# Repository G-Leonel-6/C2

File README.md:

# C2
En este repositorio se guardaran los archivos correspondientes al desarrollo de una fuente de alimentacion regulada

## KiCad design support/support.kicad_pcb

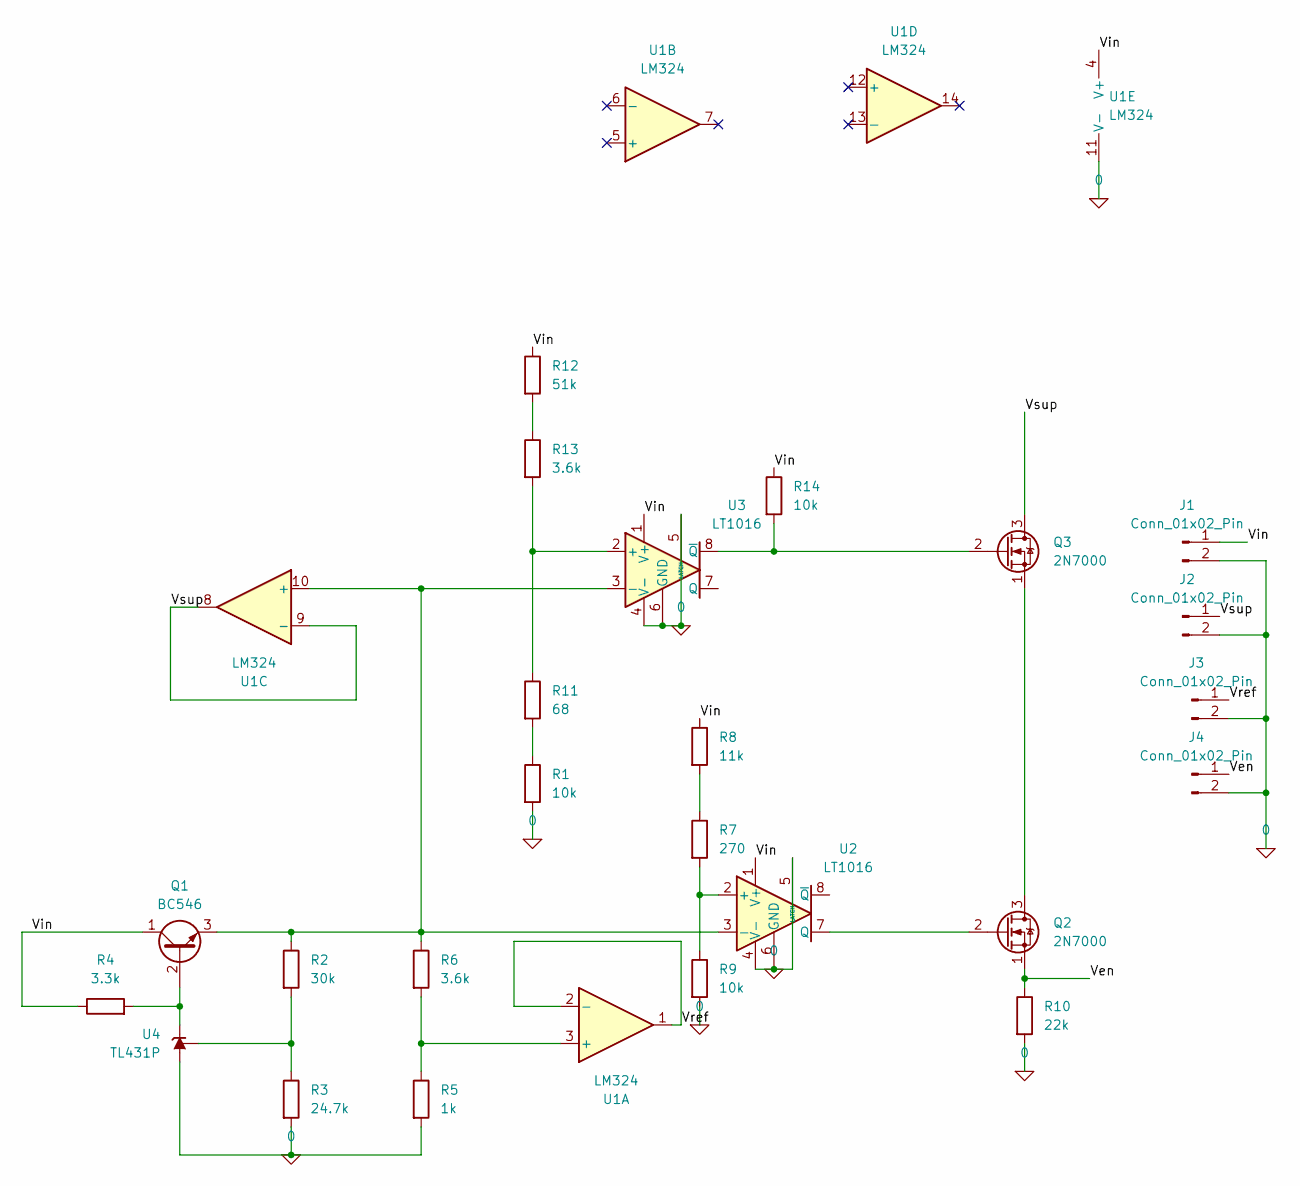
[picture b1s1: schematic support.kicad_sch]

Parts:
J1, J2, J3, J4: Conn_01x02_Pin; TerminalBlock_Altech_AK300-2_P5.00mm
Q1: BC546; TO-92_Inline
Q2, Q3: 2N7000; TO-92_Inline
R1, R9, R14: 10k; R_Axial_DIN0207_L6.3mm_D2.5mm_P10.16mm_Horizontal
R2: 30k; R_Axial_DIN0207_L6.3mm_D2.5mm_P10.16mm_Horizontal
R3: 24.7k; R_Axial_DIN0207_L6.3mm_D2.5mm_P10.16mm_Horizontal
R4: 3.3k; R_Axial_DIN0207_L6.3mm_D2.5mm_P10.16mm_Horizontal
R5: 1k; R_Axial_DIN0207_L6.3mm_D2.5mm_P10.16mm_Horizontal
R6, R13: 3.6k; R_Axial_DIN0207_L6.3mm_D2.5mm_P10.16mm_Horizontal
R7: 270; R_Axial_DIN0207_L6.3mm_D2.5mm_P10.16mm_Horizontal
R8: 11k; R_Axial_DIN0207_L6.3mm_D2.5mm_P10.16mm_Horizontal
R10: 22k; R_Axial_DIN0207_L6.3mm_D2.5mm_P10.16mm_Horizontal
R11: 68; R_Axial_DIN0207_L6.3mm_D2.5mm_P10.16mm_Horizontal
R12: 51k; R_Axial_DIN0207_L6.3mm_D2.5mm_P10.16mm_Horizontal
U1: LM324; DIP-14_W7.62mm_Socket_LongPads
U2, U3: LT1016; DIP-8_W7.62mm_Socket_LongPads
U4: TL431P; DIP-8_W7.62mm

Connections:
0: J1.2, J2.2, J3.2, J4.2, R1.2, R3.2, R5.2, R9.2, R10.2, U1.11 (V-), U2.4 (V-), U2.5 (LATCH), U2.6 (GND), U3.4 (V-), U3.5 (LATCH), U3.6 (GND), U4.6 (A)
/Ven: J4.1, Q2.1 (S), R10.1
/Vin: J1.1, Q1.1 (C), R4.1, R8.1, R12.1, R14.1, U1.4 (V+), U2.1 (V+), U3.1 (V+)
/Vref: J3.1, U1.1, U1.2 (-)
/Vsup: J2.1, Q3.3 (D), U1.8, U1.9 (-)
unnamed: Q1.2 (B), R4.2, U4.1 (K)
unnamed: Q1.3 (E), R2.1, R6.1, U1.10 (+), U2.3 (-), U3.3 (-)
unnamed: Q2.3 (D), Q3.1 (S)
unnamed: Q2.2 (G), U2.7 (Q)
unnamed: Q3.2 (G), R14.2, U3.8 (~Q)
unnamed: R1.1, R11.2
unnamed: R7.1, R8.2
unnamed: R12.2, R13.1
unnamed: R5.1, R6.2, U1.3 (+)
unnamed: R7.2, R9.1, U2.2 (+)
unnamed: R11.1, R13.2, U3.2 (+)
unnamed: R2.2, R3.1, U4.8 (REF)

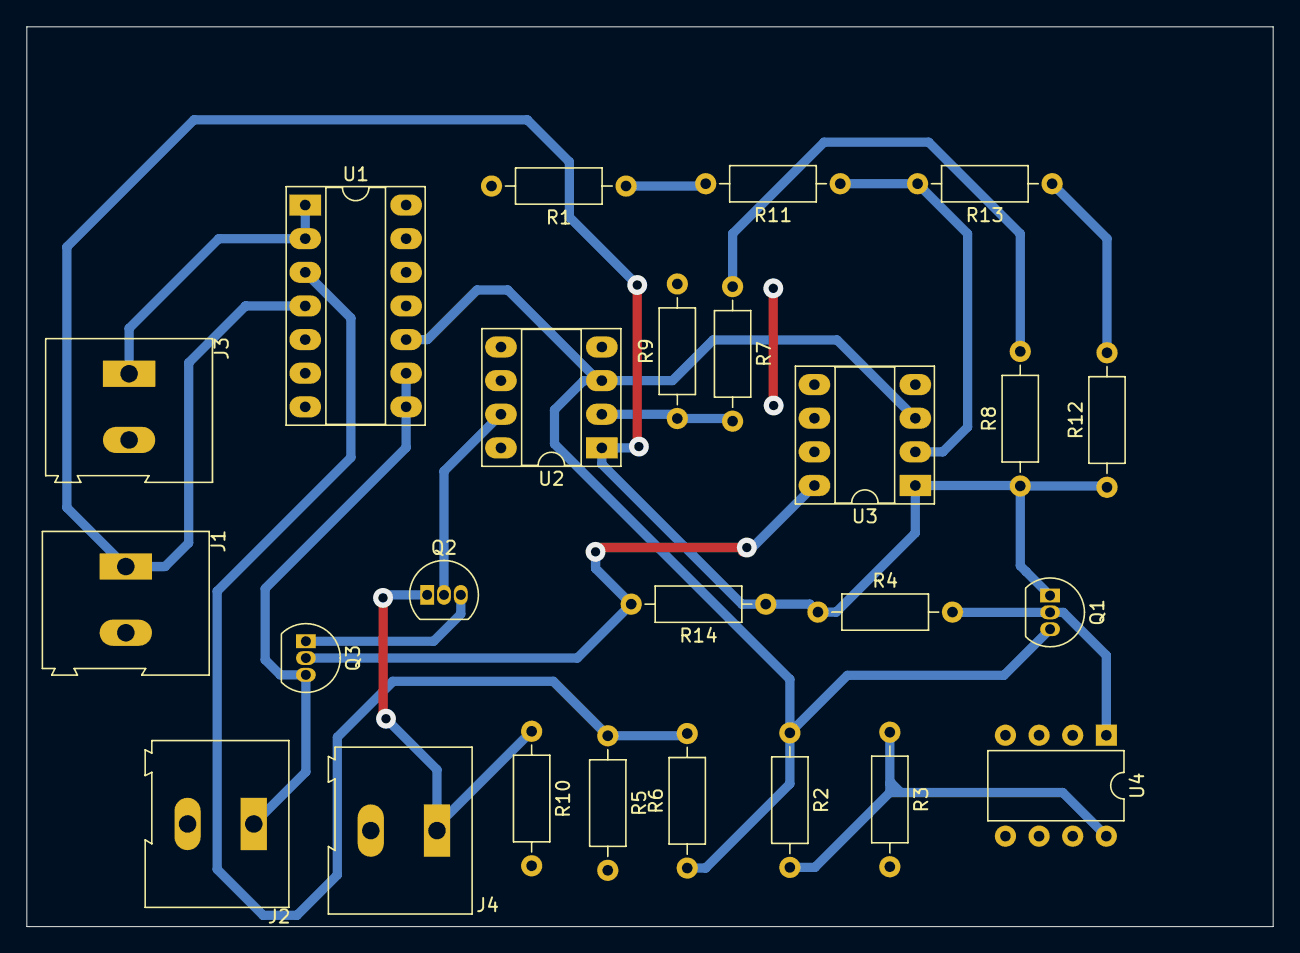
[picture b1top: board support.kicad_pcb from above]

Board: 2 copper layers, 94.1 x 68.0 mm, 25 parts (0 on the bottom side), 17 nets.

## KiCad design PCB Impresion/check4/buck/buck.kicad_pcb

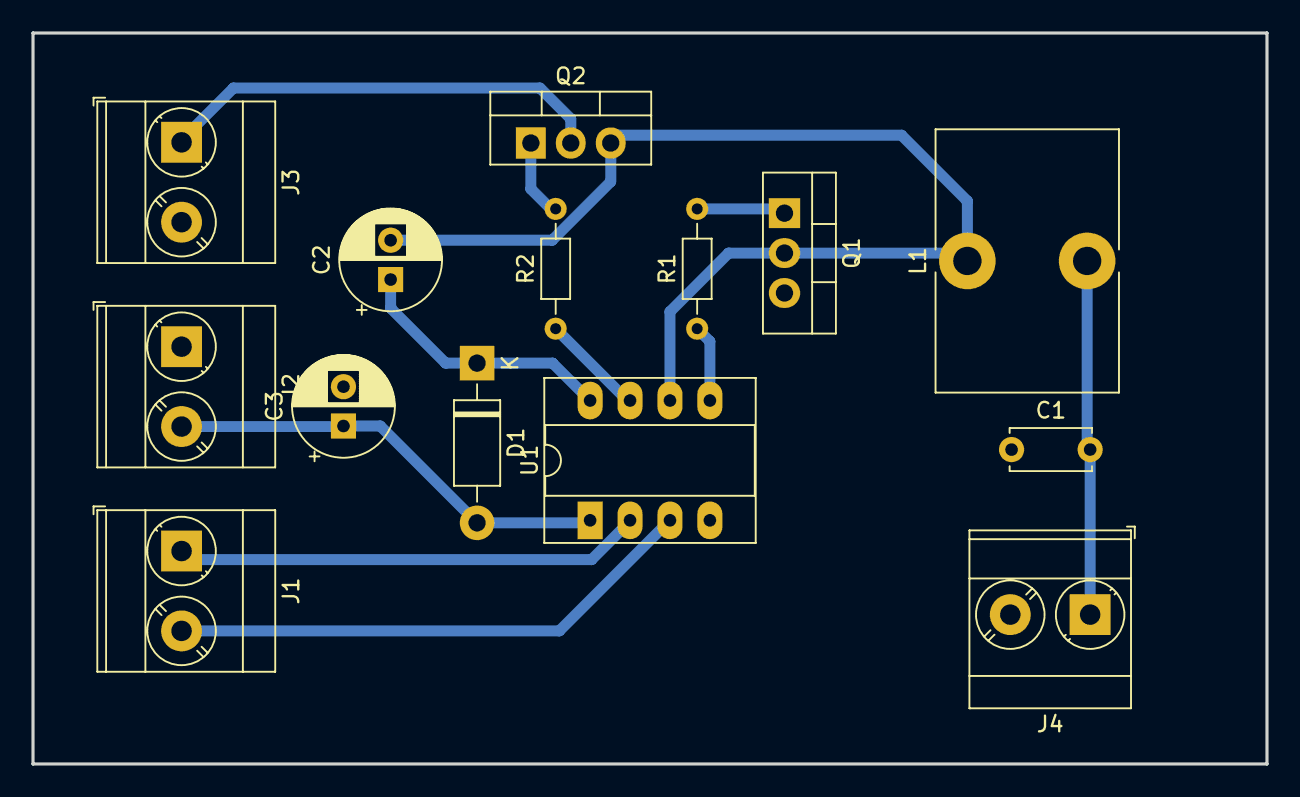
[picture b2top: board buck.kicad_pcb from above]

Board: 2 copper layers, 78.5 x 46.5 mm, 14 parts (0 on the bottom side), 12 nets.

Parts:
C1: 2.7u; C_Disc_D5.0mm_W2.5mm_P5.00mm
C2: 22u; CP_Radial_D6.3mm_P2.50mm
C3: 10u; CP_Radial_D6.3mm_P2.50mm
D1: 1N5819; D_DO-41_SOD81_P10.16mm_Horizontal
J1: V; TerminalBlock_Phoenix_MKDS-3-2-5.08_1x02_P5.08mm_Horizontal
J2: VCC; TerminalBlock_Phoenix_MKDS-3-2-5.08_1x02_P5.08mm_Horizontal
J3: VIN; TerminalBlock_Phoenix_MKDS-3-2-5.08_1x02_P5.08mm_Horizontal
J4: OUT; TerminalBlock_Phoenix_MKDS-3-2-5.08_1x02_P5.08mm_Horizontal
L1: 200u; L_Toroid_Vertical_L16.5mm_W11.4mm_P7.62mm_Pulse_KM-2
Q1, Q2: IRF3205; TO-220-3_Vertical
R1, R2: 10; R_Axial_DIN0204_L3.6mm_D1.6mm_P7.62mm_Horizontal
U1: IR2104; CERDIP-8_W7.62mm_SideBrazed_LongPads_Socket

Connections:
GND: C1.1, C3.2, J2.1, J3.1, J4.2, Q1.3 (S), U1.4 (COM)
Ho: Q2.1 (G), R2.2
Lo: Q1.1 (G), R1.2
unnamed: C2.1, D1.1 (K), U1.8 (VB)
unnamed: J1.2, U1.3 (~SD)
unnamed: J1.1, U1.2 (IN)
unnamed: J3.2, Q2.2 (D)
unnamed: C1.2, J4.1, L1.2
unnamed: R2.1, U1.7 (HO)
unnamed: R1.1, U1.5 (LO)
Vcc: C3.1, D1.2 (A), J2.2, U1.1 (VCC)
Vs: C2.2, L1.1, Q1.2 (D), Q2.3 (S), U1.6 (VS)

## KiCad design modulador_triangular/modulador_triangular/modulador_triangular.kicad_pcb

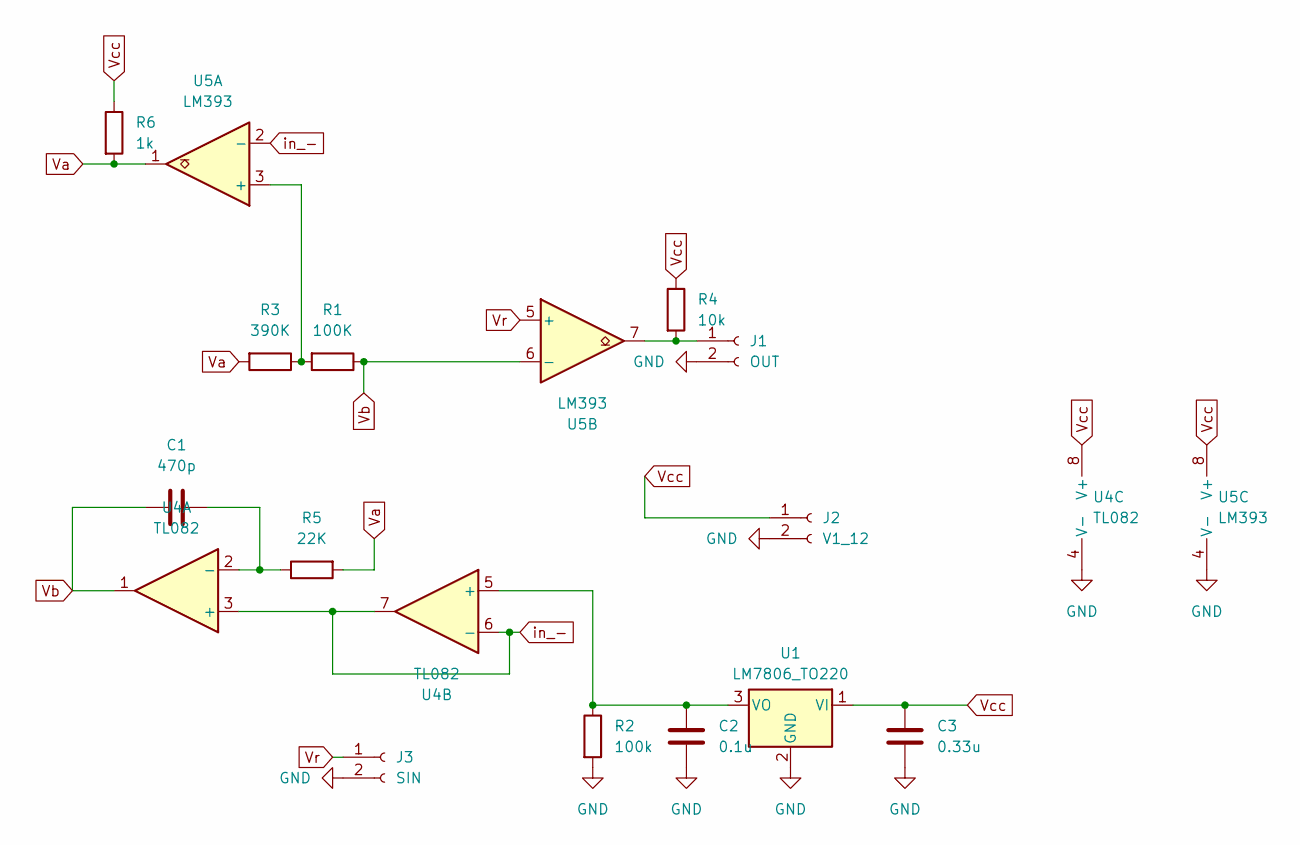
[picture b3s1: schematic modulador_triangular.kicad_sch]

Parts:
C1: 470p; C_Disc_D5.0mm_W2.5mm_P5.00mm
C2: 0.1u; C_Disc_D5.0mm_W2.5mm_P5.00mm
C3: 0.33u; C_Disc_D5.0mm_W2.5mm_P5.00mm
J1: OUT; TerminalBlock_Phoenix_MKDS-3-2-5.08_1x02_P5.08mm_Horizontal
J2: V1_12; TerminalBlock_Phoenix_MKDS-3-2-5.08_1x02_P5.08mm_Horizontal
J3: SIN; TerminalBlock_Phoenix_MKDS-3-2-5.08_1x02_P5.08mm_Horizontal
R1: 100K; R_Axial_DIN0207_L6.3mm_D2.5mm_P7.62mm_Horizontal
R2: 100k; R_Axial_DIN0207_L6.3mm_D2.5mm_P7.62mm_Horizontal
R3: 390K; R_Axial_DIN0207_L6.3mm_D2.5mm_P7.62mm_Horizontal
R4: 10k; R_Axial_DIN0207_L6.3mm_D2.5mm_P7.62mm_Horizontal
R5: 22K; R_Axial_DIN0207_L6.3mm_D2.5mm_P7.62mm_Horizontal
R6: 1k; R_Axial_DIN0207_L6.3mm_D2.5mm_P7.62mm_Horizontal
U1: LM7806_TO220; TO-220-3_Vertical
U4: TL082; DIP-8_W7.62mm_LongPads
U5: LM393; DIP-8_W7.62mm_LongPads

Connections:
GND: C2.2, C3.2, J1.2, J2.2, J3.2, R2.2, U1.2 (GND), U4.4 (V-), U5.4 (V-)
unnamed: J1.1, R4.2, U5.7
unnamed: C2.1, R2.1, U1.3 (VO), U4.5 (+)
unnamed: C1.1, R5.1, U4.2 (-)
unnamed: R1.2, R3.1, U5.3 (+)
Va: R3.2, R5.2, R6.2, U5.1
Vb: C1.2, R1.1, U4.1, U5.6 (-)
Vcc: C3.1, J2.1, R4.1, R6.1, U1.1 (VI), U4.8 (V+), U5.8 (V+)
Vr: J3.1, U5.5 (+)
in_-: U4.3 (+), U4.6 (-), U4.7, U5.2 (-)

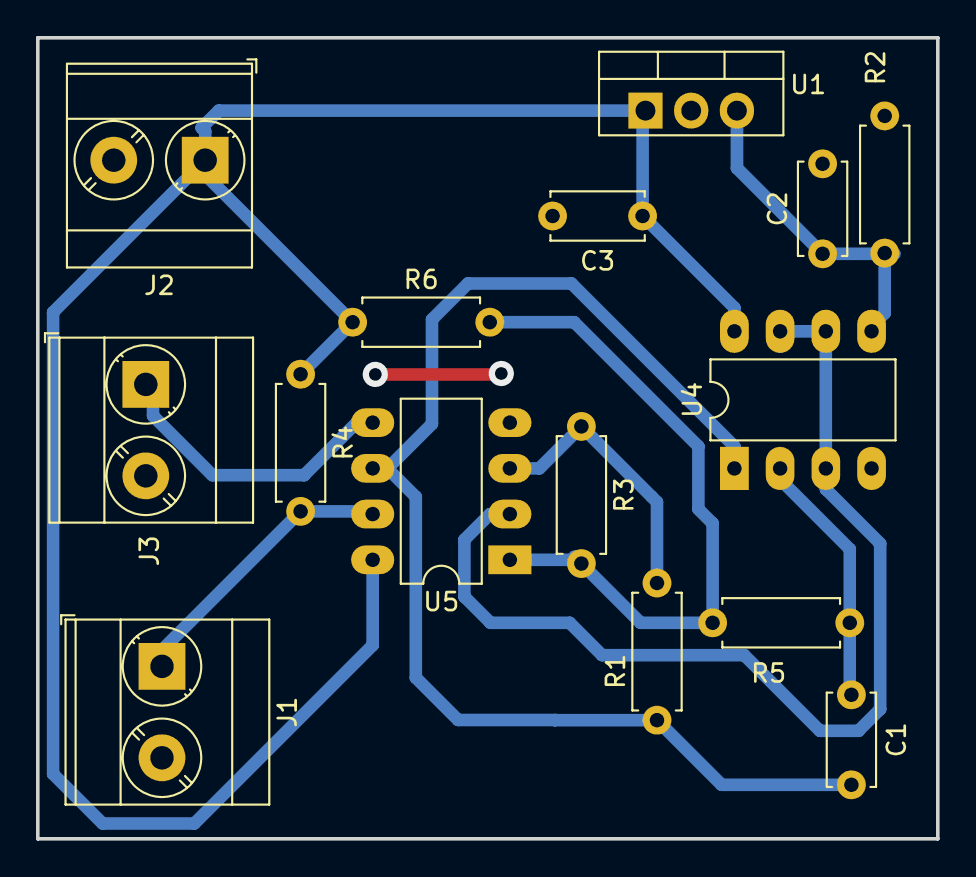
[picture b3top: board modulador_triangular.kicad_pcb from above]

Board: 2 copper layers, 50.0 x 44.5 mm, 15 parts (0 on the bottom side), 10 nets.

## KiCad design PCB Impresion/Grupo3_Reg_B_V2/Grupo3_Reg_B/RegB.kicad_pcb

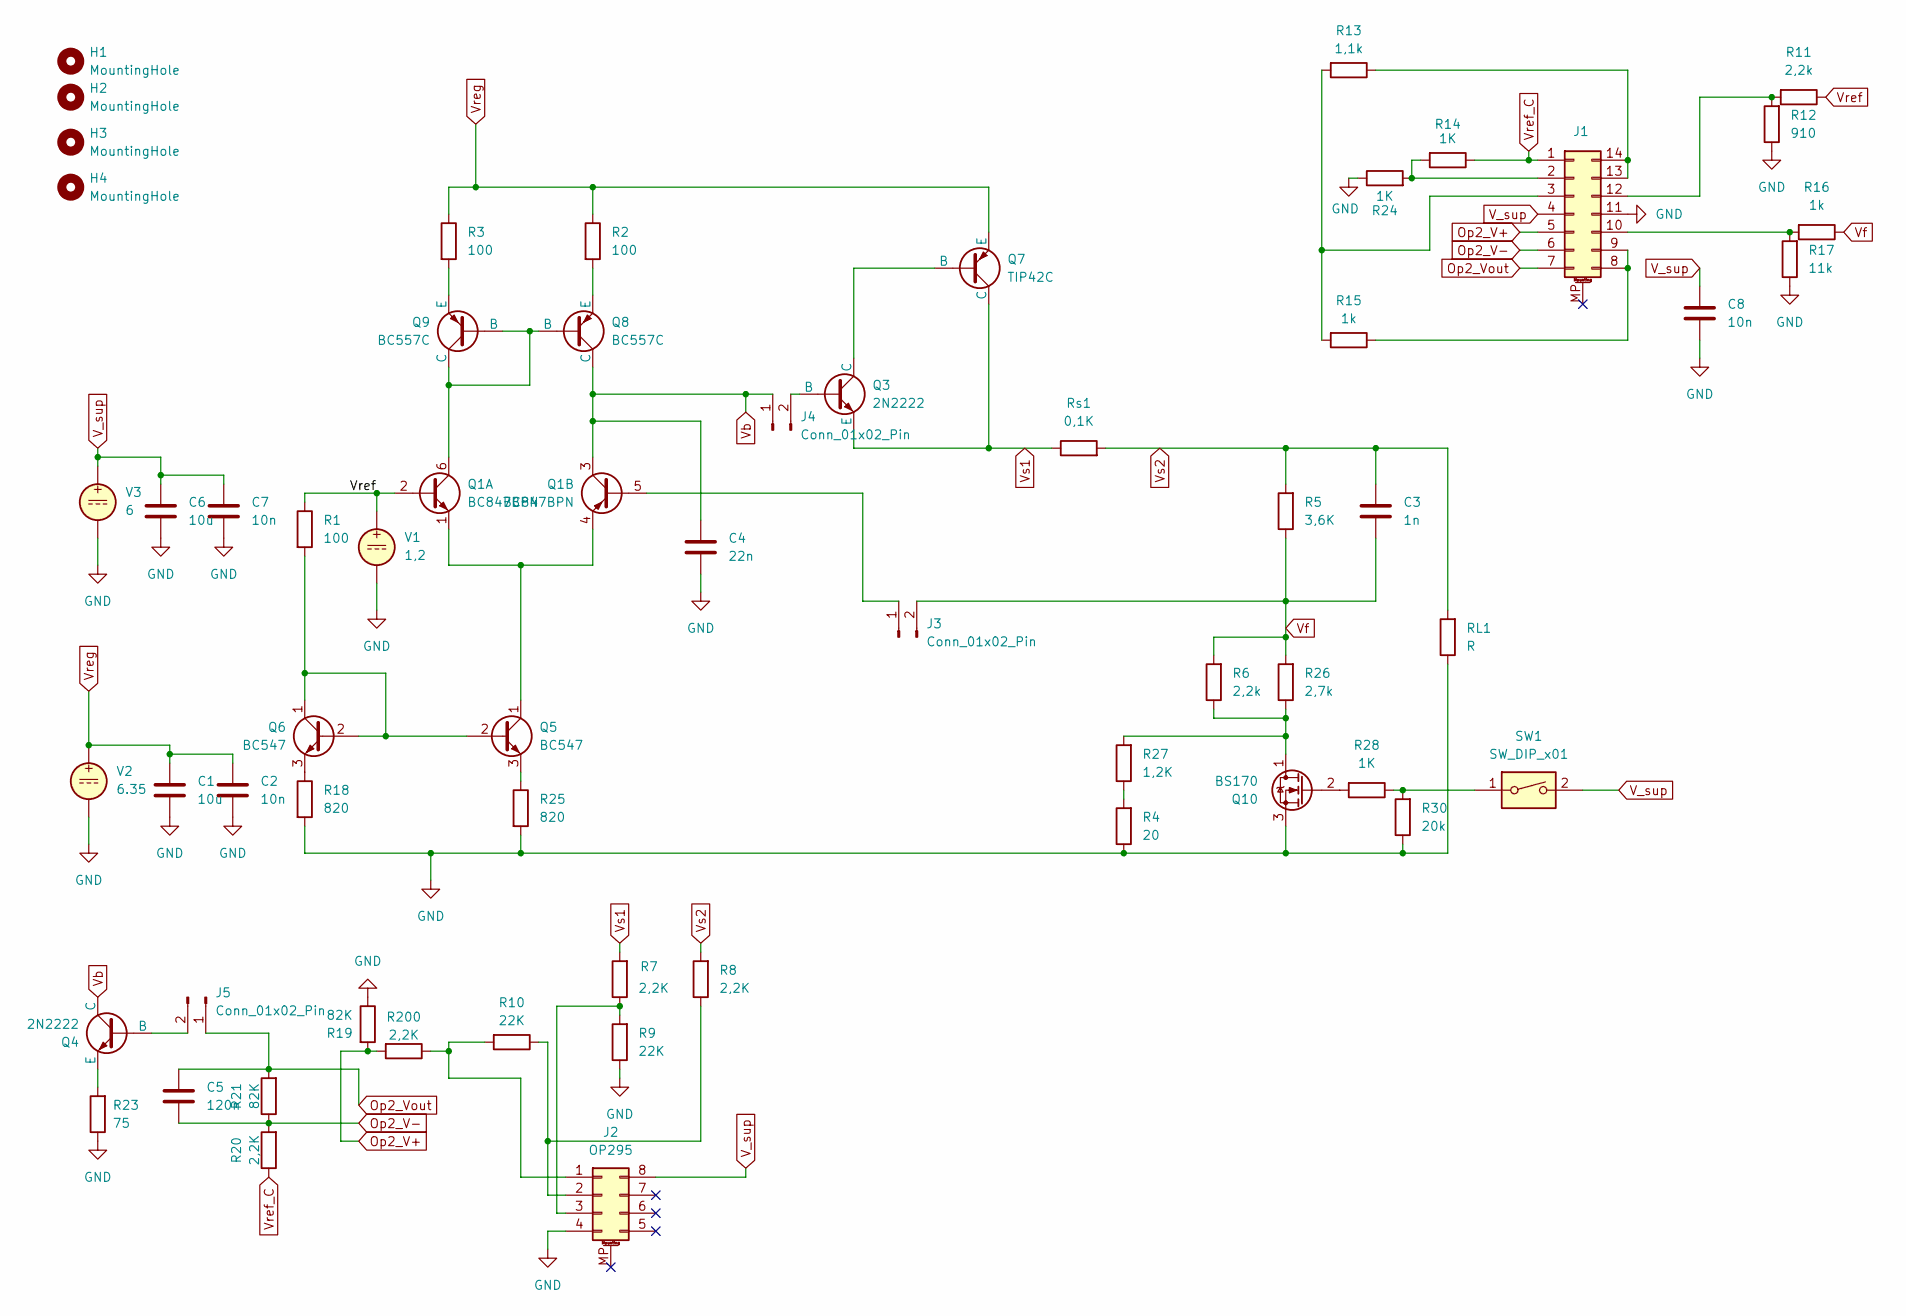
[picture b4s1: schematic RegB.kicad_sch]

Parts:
C1, C6: 10u; CP_Radial_D5.0mm_P2.00mm
C2, C7, C8: 10n; C_Disc_D5.0mm_W2.5mm_P5.00mm
C3: 1n; C_Disc_D5.0mm_W2.5mm_P5.00mm
C4: 22n; C_Disc_D5.0mm_W2.5mm_P5.00mm
C5: 120n; C_Disc_D5.0mm_W2.5mm_P5.00mm
H1, H2, H3, H4: MountingHole; MountingHole_2.7mm_M2.5
J1: Conn_02x07_Counter_Clockwise_MountingPin; DIP-14_W7.62mm
J2: OP295; DIP-8_W7.62mm
J3, J4, J5: Conn_01x02_Pin; PinHeader_1x02_P2.54mm_Vertical
Q1: BC847BPN; TSOP-6_1.65x3.05mm_P0.95mm
Q3, Q4: 2N2222; TO-92
Q5, Q6: BC547; TO-92_Inline
Q7: TIP42C; TO-220-3_Vertical
Q8, Q9: BC557C; TO-92
Q10: BS170; TO-92
R1, R2, R3: 100; R_Axial_DIN0204_L3.6mm_D1.6mm_P7.62mm_Horizontal
R4: 20; R_Axial_DIN0204_L3.6mm_D1.6mm_P7.62mm_Horizontal
R5: 3,6K; R_Axial_DIN0204_L3.6mm_D1.6mm_P7.62mm_Horizontal
R6, R11: 2,2k; R_Axial_DIN0204_L3.6mm_D1.6mm_P7.62mm_Horizontal
R7, R8, R200: 2,2K; R_Axial_DIN0204_L3.6mm_D1.6mm_P7.62mm_Horizontal
R9, R10: 22K; R_Axial_DIN0204_L3.6mm_D1.6mm_P7.62mm_Horizontal
R12: 910; R_Axial_DIN0204_L3.6mm_D1.6mm_P7.62mm_Horizontal
R13: 1,1k; R_Axial_DIN0204_L3.6mm_D1.6mm_P7.62mm_Horizontal
R14, R24: 1K; R_Axial_DIN0204_L3.6mm_D1.6mm_P7.62mm_Horizontal
R15: 1k; R_Axial_DIN0207_L6.3mm_D2.5mm_P10.16mm_Horizontal
R16: 1k; R_Axial_DIN0204_L3.6mm_D1.6mm_P7.62mm_Horizontal
R17: 11k; R_Axial_DIN0204_L3.6mm_D1.6mm_P7.62mm_Horizontal
R18, R25: 820; R_Axial_DIN0204_L3.6mm_D1.6mm_P7.62mm_Horizontal
R19, R21: 82K; R_Axial_DIN0204_L3.6mm_D1.6mm_P7.62mm_Horizontal
R20: 2,2K; R_Axial_DIN0207_L6.3mm_D2.5mm_P10.16mm_Horizontal
R23: 75; R_Axial_DIN0204_L3.6mm_D1.6mm_P7.62mm_Horizontal
R26: 2,7k; R_Axial_DIN0204_L3.6mm_D1.6mm_P7.62mm_Horizontal
R27: 1,2K; R_Axial_DIN0204_L3.6mm_D1.6mm_P7.62mm_Horizontal
R28: 1K; R_Axial_DIN0207_L6.3mm_D2.5mm_P10.16mm_Horizontal
R30: 20k; R_Axial_DIN0204_L3.6mm_D1.6mm_P7.62mm_Horizontal
RL1: R; TerminalBlock_Phoenix_MKDS-3-2-5.08_1x02_P5.08mm_Horizontal
Rs1: 0,1K; R_Axial_Power_L20.0mm_W6.4mm_P25.40mm
SW1: SW_DIP_x01; Molex_KK-254_AE-6410-02A_1x02_P2.54mm_Vertical
V1: 1,2; TerminalBlock_Phoenix_MKDS-3-2-5.08_1x02_P5.08mm_Horizontal
V2: 6.35; TerminalBlock_Phoenix_MKDS-3-2-5.08_1x02_P5.08mm_Horizontal
V3: 6; TerminalBlock_Phoenix_MKDS-3-2-5.08_1x02_P5.08mm_Horizontal

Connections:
GND: C1.2, C2.2, C4.2, C6.2, C7.2, C8.2, J1.11, J2.4, Q10.3 (S), R4.1, R9.1, R12.1, R17.1, R18.2, R19.1, R23.1, R24.1, R25.2, R30.1, RL1.1, V1.2, V2.2, V3.2
unnamed: J1.2, R14.2, R24.2
unnamed: J1.3, R13.2, R15.2
unnamed: J1.8, J1.9, R15.1
unnamed: J1.10, R16.2, R17.2
unnamed: J1.12, R11.2, R12.2
unnamed: J1.13, J1.14, R13.1
unnamed: J2.1, R10.2, R200.1
unnamed: J2.2, R8.1, R10.1
unnamed: J2.3, R7.1, R9.2
unnamed: J3.1, Q1.5 (B2)
unnamed: J4.2, Q3.2 (B)
unnamed: J5.2, Q4.2 (B)
unnamed: Q1.6 (C1), Q8.2 (B), Q9.1 (C), Q9.2 (B)
unnamed: Q1.1 (E1), Q1.4 (E2), Q5.1 (C)
unnamed: Q3.1 (C), Q7.2 (B)
unnamed: Q4.3 (E), R23.2
unnamed: Q5.2 (B), Q6.1 (C), Q6.2 (B), R1.2
unnamed: Q5.3 (E), R25.1
unnamed: Q6.3 (E), R18.1
unnamed: Q8.3 (E), R2.2
unnamed: Q9.3 (E), R3.2
unnamed: Q10.1 (D), R6.1, R26.1, R27.2
unnamed: Q10.2 (G), R28.2
unnamed: R4.2, R27.1
unnamed: R28.1, R30.2, SW1.1
Op2_V+: J1.5, R19.2, R200.2
Op2_V-: C5.2, J1.6, R20.2, R21.1
Op2_Vout: C5.1, J1.7, J5.1, R21.2
V_sup: C6.1, C7.1, C8.1, J1.4, J2.8, SW1.2, V3.1
Vb: C4.1, J4.1, Q1.3 (C2), Q4.1 (C), Q8.1 (C)
Vf: C3.2, J3.2, R5.1, R6.2, R16.1, R26.2
Vref: Q1.2 (B1), R1.1, R11.1, V1.1
Vref_C: J1.1, R14.1, R20.1
Vreg: C1.1, C2.1, Q7.3 (E), R2.1, R3.1, V2.1
Vs1: Q3.3 (E), Q7.1 (C), R7.2, Rs1.1
Vs2: C3.1, R5.2, R8.2, RL1.2, Rs1.2

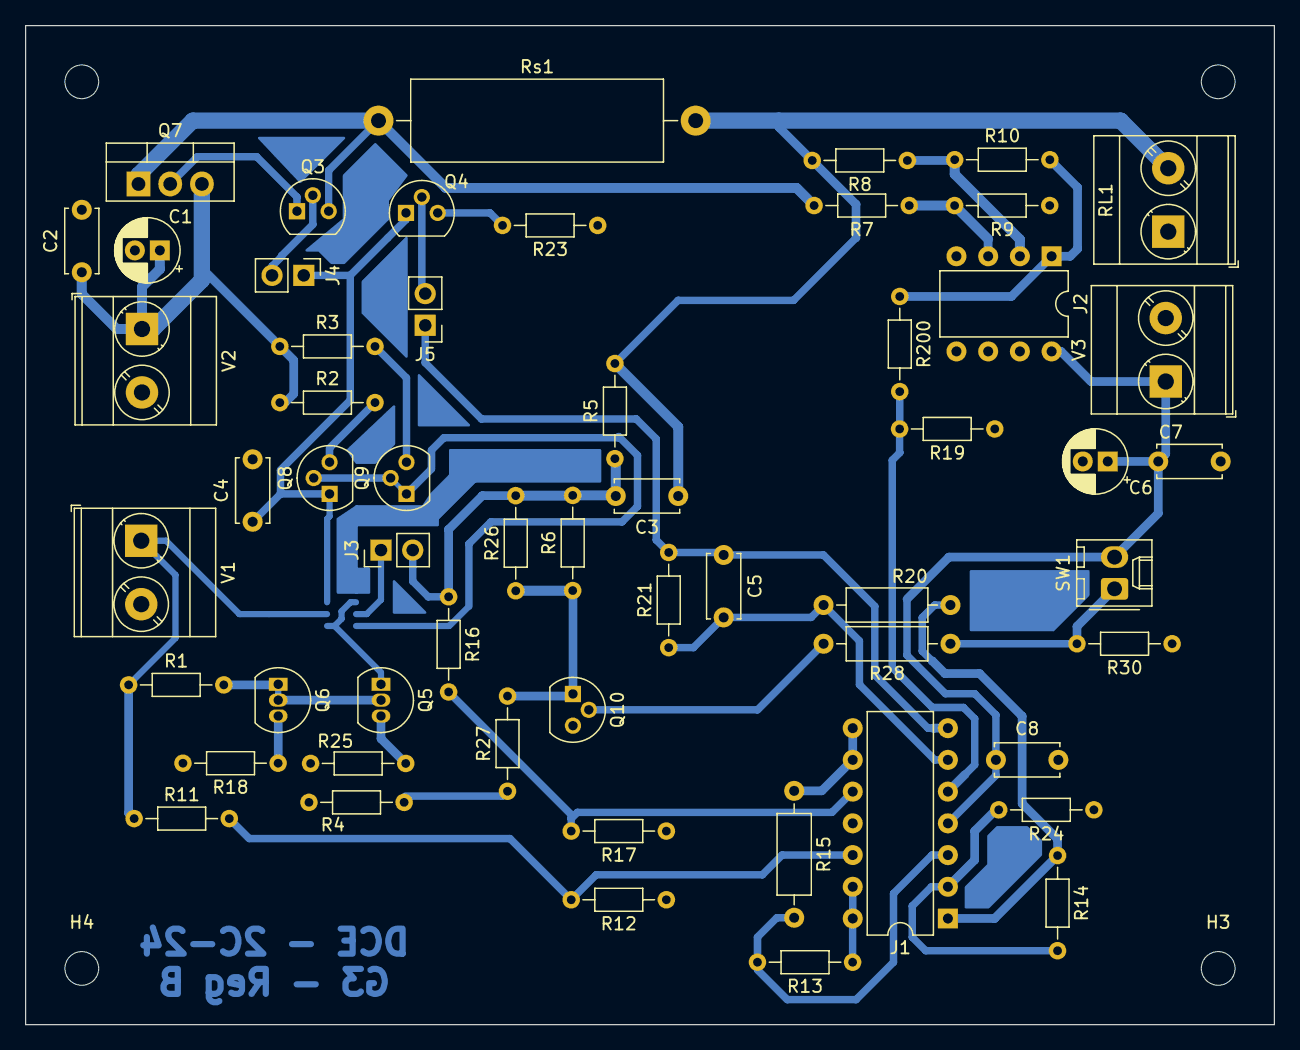
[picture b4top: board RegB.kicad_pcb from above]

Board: 2 copper layers, 100.0 x 80.0 mm, 61 parts (1 on the bottom side), 37 nets.

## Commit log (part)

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2024-09-09 agrego esquematico gral del regulador lineal, cumple con regulacion de tension y corriente en regulador B
2024-09-09 cambio pequeño en esquematico, correccion de path de librerias
2024-09-10 Modificación en la realimententación
    Modifique la resistencia de realimentación para mejorar el ajuste en 3,3V
2024-09-11 agrego script para generar imagenes y las primeras imagenes obtenidas
2024-09-12 correccion en esquematico agrego imagenes de ganancias de lazo
2024-09-12 me olvide guardar un cambio
2024-09-13 imagenes del regulador A
2024-09-13 me olvide de guardar unos cambios
2024-09-13 cambios de opam
2024-09-13 ajuste minimo para foldback
2024-09-13 cambios en imagenes
2024-09-19 prueba git
2024-09-19 analisis transitorio
2024-09-20 cambios estabilidad
2024-09-21 ordene el repo
2024-09-21 pruebas de estabilizacion
2024-09-21 lazo de tension compensado
2024-09-21 lazo de corriente posiblemente estabilizado
2024-09-22 git cambios menores regulador B
2024-09-22 estabilizacion regulador A
2024-09-23 agrego simulaciones para la potencia
2024-09-23 preparo codigo para graficar imagenes
2024-09-25 simulaciones regulador A
2024-09-25 agrego imagenes del regulador B
2024-09-25 agrego imagenes adicionales
2024-09-26 imagen adicional
2024-09-26 avance del pcb
2024-09-27 imagenes reg a
2024-09-27 primer commit de juli
2024-09-30 cambios con nuevo op
2024-09-30 modificacion de pcb
2024-09-30 caps de filtro de ruido de linea
2024-10-02 ultimas variaciones de la placa para imprimir
2024-10-06 verificacion de simulaciones
2024-10-06 verificacion de simulaciones me olvide gaurdar algo
2024-10-15 cambios sobre la marcha
2024-10-17 subo archivo graficar 2 para realizar graficos el checkpoint 3
2024-10-18 agregue imagenes para checkpoint 3 falta ordenar
2024-11-03 arreglando
2024-11-03 placa de kicad
2024-11-03 actualizacion de placa
2024-11-03 commit express
2024-11-03 pcb del pwm
2024-11-04 cambios menores
2024-11-05 pcb de buck
2024-11-06 agrego simulaciones de la buck
2024-11-07 modificaciones de pcb del pwm
2024-11-08 esto causo muchos problemas
2024-11-08 configuracion de lfs creo
2024-11-08 txt de las simulaciones
2024-11-08 agrego simulaciones de buck
2024-11-10 modificaciones PWM
2024-11-10 mini arreglo
2024-11-11 modificaciones de trazas
2024-11-13 support
2024-11-13 modificaciones en la support
2024-11-13 gate driver para la buck
2024-11-14 mas imagenes
2024-11-14 pcb del regulador buck
2024-11-14 pcb buck
2024-11-15 txt buck agregado
2024-11-15 haciendo imagenes
2024-12-03 cambios de simulacion viejos
2024-12-03 arregle algo de la buck
2024-12-04 pcb support
